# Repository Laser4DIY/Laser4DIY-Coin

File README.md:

# Laser4DIY-Coin
Laser4DIY Coin Demo PCB

Little RGB LED ring for testing the Laser4DIY PCB laser:
- 12x WS2812 compatible adressable 1515 LEDs
- Attinyx5 (.., 45, 85) as controller
- 17mm Diameter
- one copper layer 

---
This source describes Open Hardware and is licensed under the CERN-OHL-P v2

You may redistribute and modify this documentation and make products using it under the terms of the CERN-OHL-P v2 (https:/cern.ch/cern-ohl). This documentation is distributed WITHOUT ANY EXPRESS OR IMPLIED WARRANTY, INCLUDING OF MERCHANTABILITY, SATISFACTORY QUALITY AND FITNESS FOR A PARTICULAR PURPOSE. Please see the CERN-OHL-P v2 for applicable conditions

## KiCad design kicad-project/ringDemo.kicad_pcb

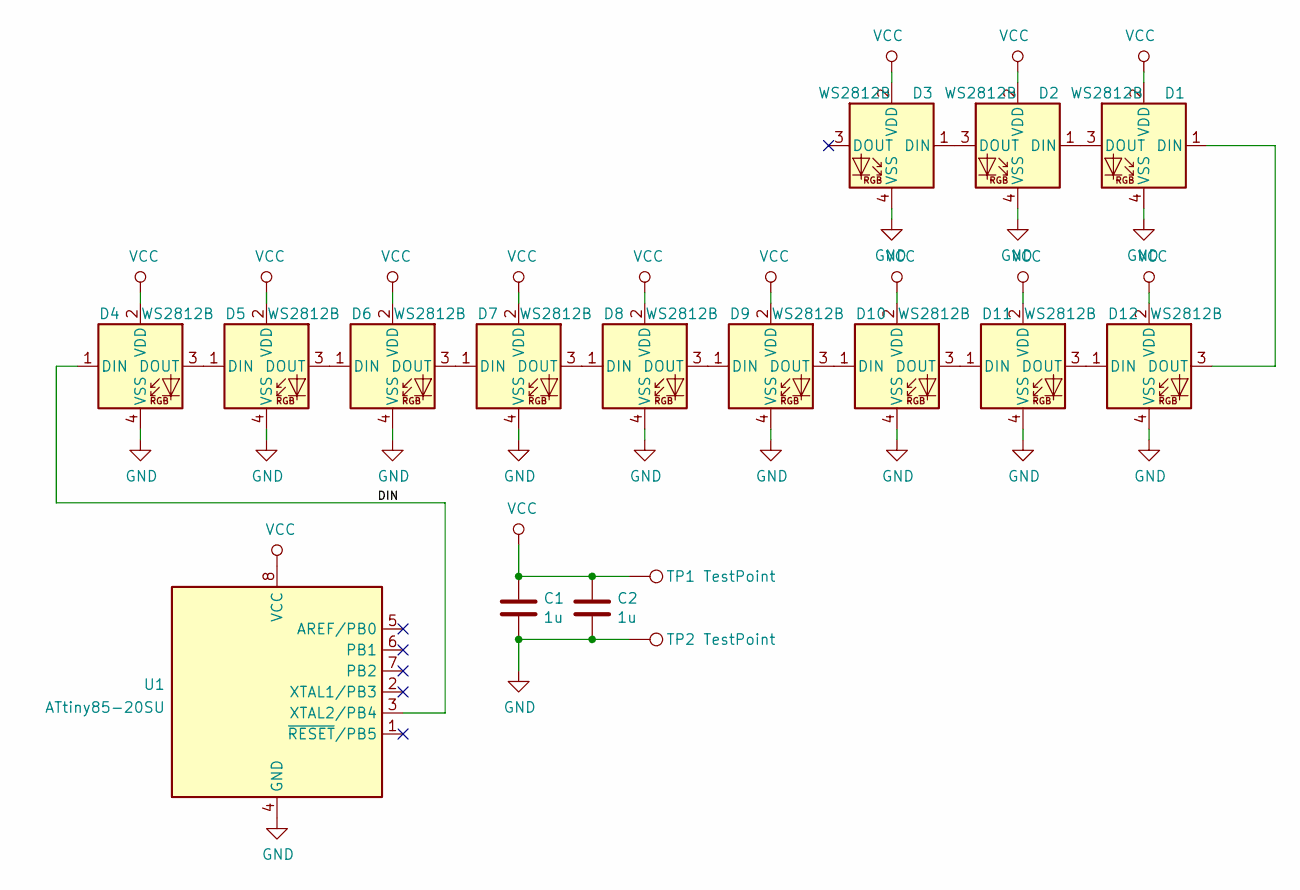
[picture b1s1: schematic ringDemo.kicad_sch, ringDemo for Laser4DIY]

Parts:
C1, C2: 1u; C_0402_min
D1, D2, D3, D4, D5, D6, D7, D8, D9, D10, D11, D12: WS2812B; LED_SK6812_EC15_1.5x1.5mm_modRounded
TP1, TP2: TestPoint; TestPoint_Pad_D1.0mm
U1: ATtiny85-20SU; SOIJ-8_5.3x5.3mm_P1.27mm

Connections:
/DIN: D4.1 (DIN), U1.3 (XTAL2/PB4)
GND: C1.2, C2.2, D1.4 (VSS), D2.4 (VSS), D3.4 (VSS), D4.4 (VSS), D5.4 (VSS), D6.4 (VSS), D7.4 (VSS), D8.4 (VSS), D9.4 (VSS), D10.4 (VSS), D11.4 (VSS), D12.4 (VSS), TP2.1, U1.4 (GND)
unnamed: D1.1 (DIN), D12.3 (DOUT)
unnamed: D1.3 (DOUT), D2.1 (DIN)
unnamed: D2.3 (DOUT), D3.1 (DIN)
unnamed: D4.3 (DOUT), D5.1 (DIN)
unnamed: D5.3 (DOUT), D6.1 (DIN)
unnamed: D6.3 (DOUT), D7.1 (DIN)
unnamed: D7.3 (DOUT), D8.1 (DIN)
unnamed: D8.3 (DOUT), D9.1 (DIN)
unnamed: D9.3 (DOUT), D10.1 (DIN)
unnamed: D10.3 (DOUT), D11.1 (DIN)
unnamed: D11.3 (DOUT), D12.1 (DIN)
VCC: C1.1, C2.1, D1.2 (VDD), D2.2 (VDD), D3.2 (VDD), D4.2 (VDD), D5.2 (VDD), D6.2 (VDD), D7.2 (VDD), D8.2 (VDD), D9.2 (VDD), D10.2 (VDD), D11.2 (VDD), D12.2 (VDD), TP1.1, U1.8 (VCC)

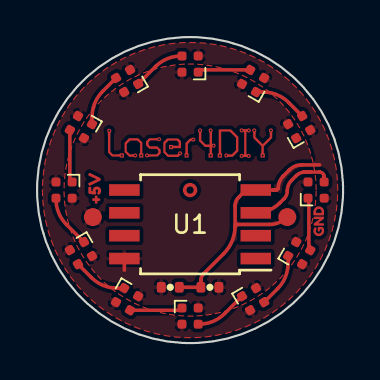
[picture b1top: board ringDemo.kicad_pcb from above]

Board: 2 copper layers, 17.0 x 17.0 mm, 20 parts (0 on the bottom side), 14 nets.

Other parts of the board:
G1: LOGO; logo2_10mm
kibuzzard-623DBD1B: G***; kibuzzard-623DBD1B
kibuzzard-623DBE1D: G***; kibuzzard-623DBE1D

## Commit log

2022-03-28 Update README.md
    fix typos
2022-03-30 PCB-Files and License
    Added PCB Files (Kicad Gerber and some PDFs)
    Added License Information
2022-03-30 testing with gitignore
2022-04-19 added isolation svg
2022-04-19 centered svg on page
2022-04-19 Variant with smaller clearances
    Added variant with smaller clearances
2023-03-09 cleanup svg
2023-06-20 added front mask svg and pdf
2023-06-21 test mask for exposing solder mask film
